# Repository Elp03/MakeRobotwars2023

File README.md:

# MakeRobotwars2023
MAKE robotwars 

Pins that work on an esp 32
  D32 - PMW port
  D33 - PMW port 
  D35 - not a PMW port but acctualy works with analogread
  D34 - works not used for PMW or analog read
  D39 - Named VN(why?) perfect for boleans
  D36 - Named VP(why? i dont know)  perfect for boleans
Pins that does not wort with ESP_NOW
  D25 
  D26 not work, 
  dont thing adc2 works with esp32

  Controller 
  Joystick 
      x: D34 
      y: D35
  Buttons
      Start/stopp robot: D39
      Start/stopp wepon: D36
  Potmeter
      pot: D33

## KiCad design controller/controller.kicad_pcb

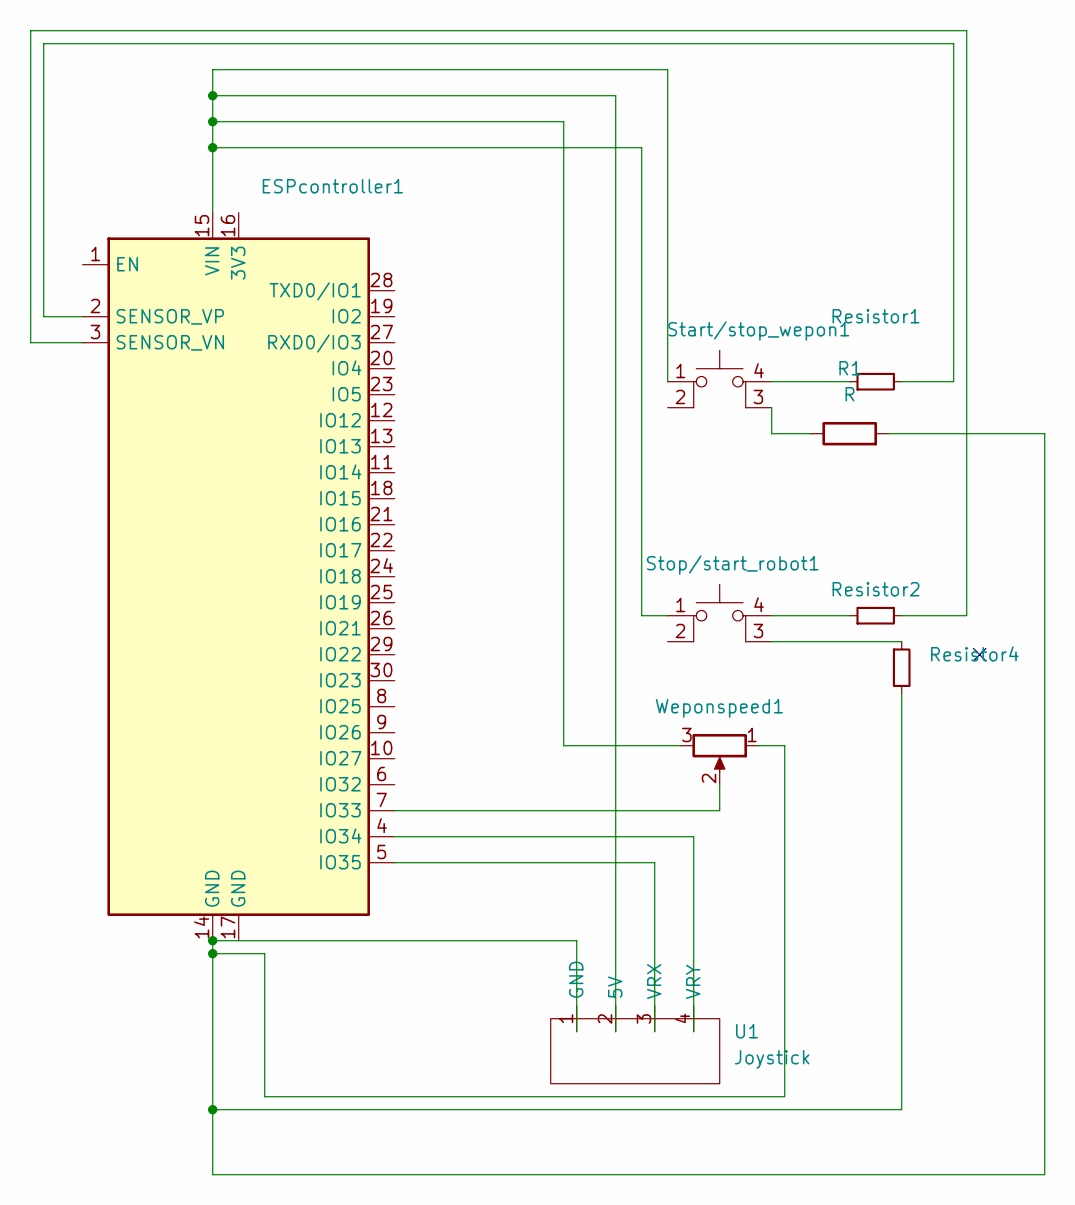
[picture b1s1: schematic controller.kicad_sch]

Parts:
ESPcontroller1: ESP32_DevKit_V1_DOIT; esp32_devkit_v1_doit
R1: R; R_Axial_DIN0309_L9.0mm_D3.2mm_P15.24mm_Horizontal
Resistor1, Resistor2, Resistor4: R_Small; R_Axial_DIN0309_L9.0mm_D3.2mm_P15.24mm_Horizontal
Start/stop_wepon1: SW_MEC_5E; SW_Push_2P1T_Toggle_CK_PVA1xxH4xxxxxxV2
Stop/start_robot1: SW_MEC_5E; SW_Push_2P1T_Toggle_CK_PVA1xxH3xxxxxxV2
U1: Joystick; PinSocket_1x04_P2.54mm_Vertical
Weponspeed1: R_Potentiometer; PinSocket_1x03_P2.54mm_Vertical

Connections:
unnamed: ESPcontroller1.2 (SENSOR_VP), Resistor1.2
unnamed: ESPcontroller1.3 (SENSOR_VN), Resistor2.2
unnamed: ESPcontroller1.4 (IO34), U1.4 (VRY)
unnamed: ESPcontroller1.5 (IO35), U1.3 (VRX)
unnamed: ESPcontroller1.7 (IO33), Weponspeed1.2
unnamed: ESPcontroller1.14 (GND), R1.2, Resistor4.2, U1.1 (GND), Weponspeed1.1
unnamed: ESPcontroller1.15 (VIN), Start/stop_wepon1.1, Stop/start_robot1.1, U1.2 (5V), Weponspeed1.3
unnamed: R1.1, Start/stop_wepon1.3 (K)
unnamed: Resistor1.1, Start/stop_wepon1.4 (A)
unnamed: Resistor2.1, Stop/start_robot1.4 (A)
unnamed: Resistor4.1, Stop/start_robot1.3 (K)

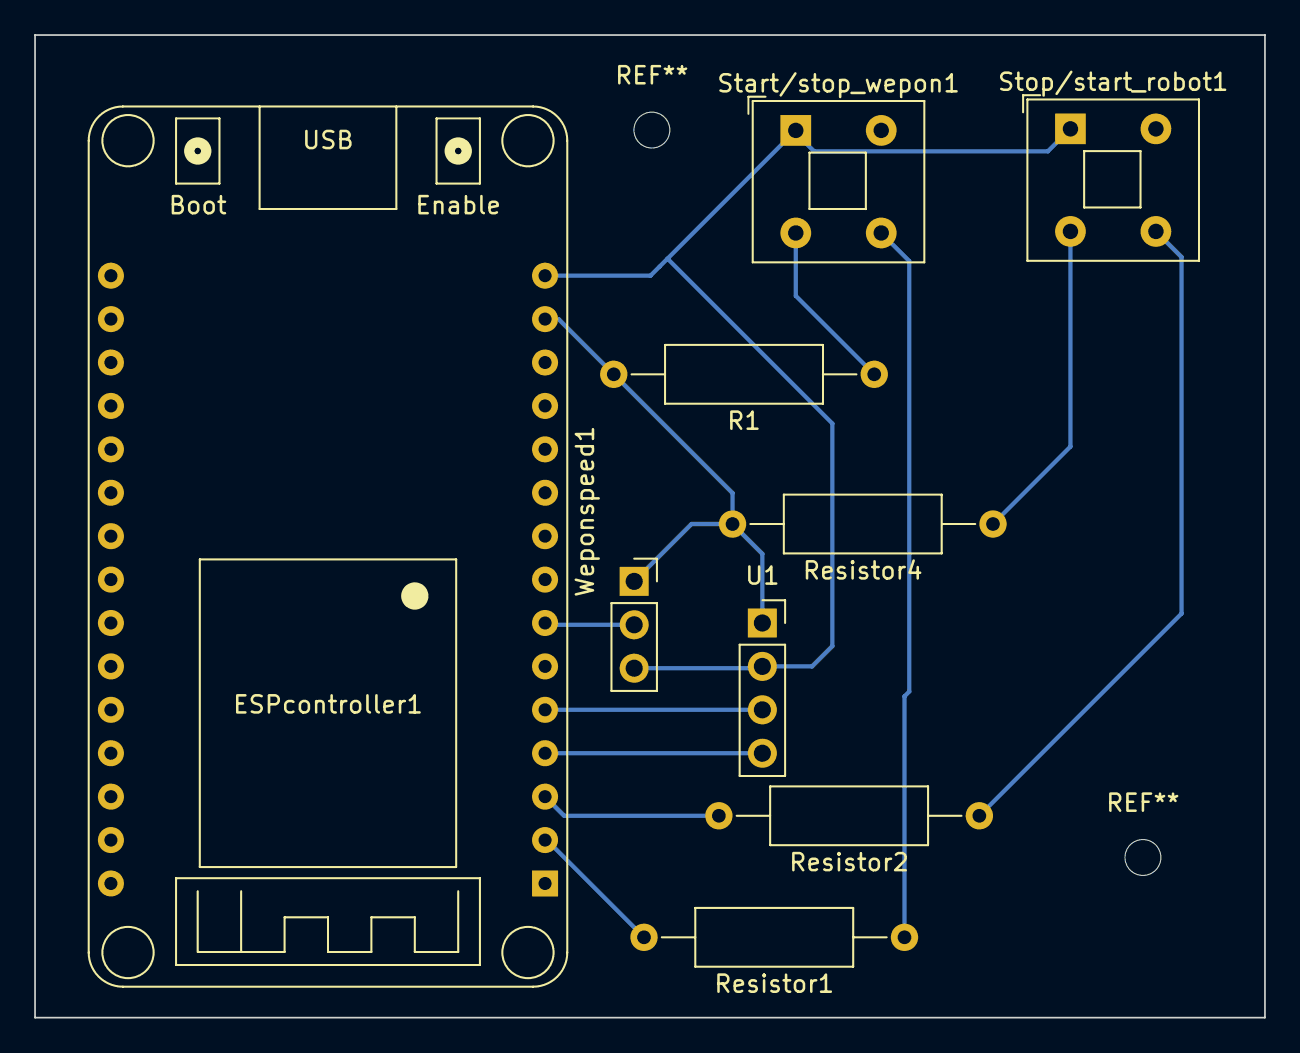
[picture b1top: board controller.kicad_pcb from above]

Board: 2 copper layers, 72.0 x 57.5 mm, 9 parts (0 on the bottom side), 11 nets.

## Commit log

2023-09-16 Platformio uppsett
2023-09-16 Filled out the configuration file
2023-09-23 Update README.md
    Overview over pins we can use
2023-09-23 Robot interface created. Will be designing receiver code and PCB in the next step.
2023-10-04 checked sensors ports and if the circut worked
2023-10-04 some small changes
2023-10-04 Programmed the controller code
2023-10-04 Made it pretty
2023-10-04 Merged robot into main, fixed the code as well
2023-10-04 added the pcb design for the controller
2023-10-15 kaos
2023-10-15 added gitignore for pcb files
2023-10-15 sorting the kaos
2023-10-15 Added rough draft for receiver class
2023-10-15 Rough draft on receiver code
2023-10-25 Reinstated the old transmitter/receiver code, will be developing the robot's receiver on the robot branch.
2023-10-25 A rough draft for the controller part of the robot. Currently focusing on the movement part.
2023-10-29 More receiver code, stuff is still not working
2023-11-03 magic
    fix horrible kode base
